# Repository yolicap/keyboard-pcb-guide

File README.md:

Following along to [ruiqimao/keyboard-pcb-guide](https://github.com/ruiqimao/keyboard-pcb-guide)

i found out you can add gifs to readmes and now i cant stop

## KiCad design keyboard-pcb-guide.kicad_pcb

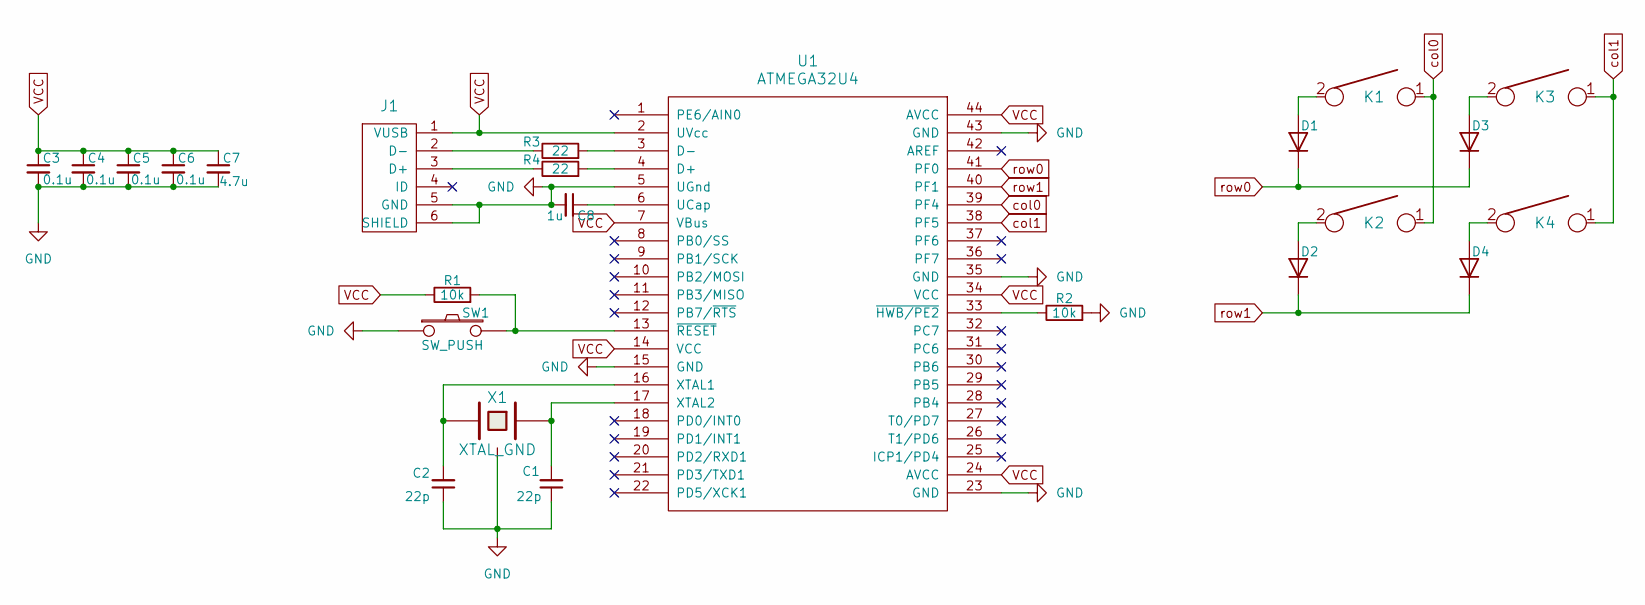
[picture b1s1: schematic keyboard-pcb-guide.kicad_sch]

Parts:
C1, C2: 22p; C_0805_2012Metric_Pad1.18x1.45mm_HandSolder
C3, C4, C5, C6: 0.1u; C_0805_2012Metric_Pad1.18x1.45mm_HandSolder
C7: 4.7u; C_0805_2012Metric_Pad1.18x1.45mm_HandSolder
C8: 1u; C_0805_2012Metric_Pad1.18x1.45mm_HandSolder
D1, D2, D3, D4: D; D_SOD123_axial
J1: USB_mini_micro_B; USB_miniB_hirose_5S8
K1, K2, K3, K4: KEYSW; Mx_Alps_100
R1, R2: 10k; R_0805_2012Metric_Pad1.20x1.40mm_HandSolder
R3, R4: 22; R_0805_2012Metric_Pad1.20x1.40mm_HandSolder
SW1: SW_PUSH; SW_SPST_TL3342
U1: ATMEGA32U4; TQFP-44_10x10mm_P0.8mm
X1: XTAL_GND; Crystal_SMD_SeikoEpson_FA238-4Pin_3.2x2.5mm

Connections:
GND: C1.1, C2.1, C3.2, C4.2, C5.2, C6.2, C7.2, C8.2, J1.5 (GND), J1.6 (SHIELD), R2.2, SW1.1, U1.5 (UGnd), U1.15 (GND), U1.23 (GND), U1.35 (GND), U1.43 (GND), X1.3
unnamed: D1.2 (A), K1.2
unnamed: D2.2 (A), K2.2
unnamed: D3.2 (A), K3.2
unnamed: D4.2 (A), K4.2
unnamed: J1.3 (D+), R4.1
unnamed: J1.2 (D-), R3.1
unnamed: R4.2, U1.4 (D+)
unnamed: R3.2, U1.3 (D-)
unnamed: C8.1, U1.6 (UCap)
unnamed: C2.2, U1.16 (XTAL1), X1.2
unnamed: C1.2, U1.17 (XTAL2), X1.1
unnamed: R2.1, U1.33 (~HWB/PE2)
unnamed: R1.2, SW1.2, U1.13 (~RESET)
VCC: C3.1, C4.1, C5.1, C6.1, C7.1, J1.1 (VUSB), R1.1, U1.2 (UVcc), U1.7 (VBus), U1.14 (VCC), U1.24 (AVCC), U1.34 (VCC), U1.44 (AVCC)
col0: K1.1, K2.1, U1.39 (PF4)
col1: K3.1, K4.1, U1.38 (PF5)
row0: D1.1 (K), D3.1 (K), U1.41 (PF0)
row1: D2.1 (K), D4.1 (K), U1.40 (PF1)

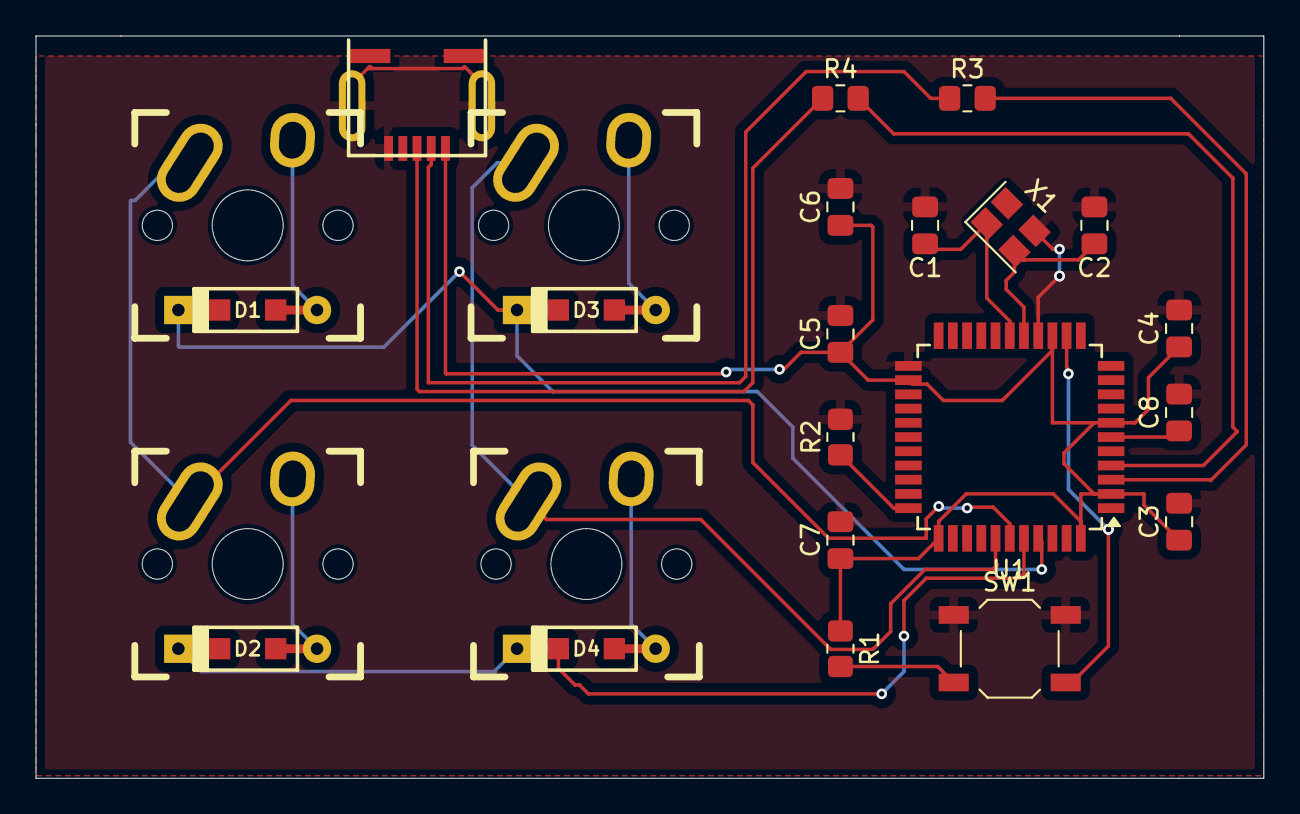
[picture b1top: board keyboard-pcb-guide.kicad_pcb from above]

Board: 2 copper layers, 69.1 x 41.8 mm, 24 parts (0 on the bottom side), 19 nets.

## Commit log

2024-07-18 progress so far
